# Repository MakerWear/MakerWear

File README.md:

# MakerWear
MakerWear is a tangible and modular, wearable construction kit for young children that contains two parts: (1) a set of single-function, plug-and-play modules that could be combined to create complex interactive behaviors; (2) magnetic socket meshes that are pre-sewn into clothing that provides an easy method to attach and detach modules to clothes.

This repository contains all of the source files that are required to build or modify MakerWear modules in addition to the socket mesh.

# Repository Organization
For example, take the MultiColor Light as an example. Similar to almost all other modules, the MultiColor Light is a 1x3 module which means that it has one input and three outputs and requires two PCBs to build. The bottom PCB is found here: https://github.com/MakerWear/MakerWear/tree/master/Common/BasePCBs/1x3/Bottom and the Top PCB (along with the rest of the source files that are specifically designed for this module) is found here: https://github.com/MakerWear/MakerWear/tree/master/Modules/Action/MultiColorLight

The ComponentList.xlsx contains all of the components and links to the vendors from which you can buy them. the .brd file (board layout) should always be next the the .sch file (board schematics).

Each module has a microcontroller which could be programmed using an Arduino. the arduino source file is inside the https://github.com/MakerWear/MakerWear/tree/master/Modules/Action/MultiColorLight/ArduinoCodes folder. and finally, there is an illustrator file which is used to cut/etch a piece of colored cardboard (e.g. white, red, black, blue for action, power, sensor and modifier) using a laser cutter.

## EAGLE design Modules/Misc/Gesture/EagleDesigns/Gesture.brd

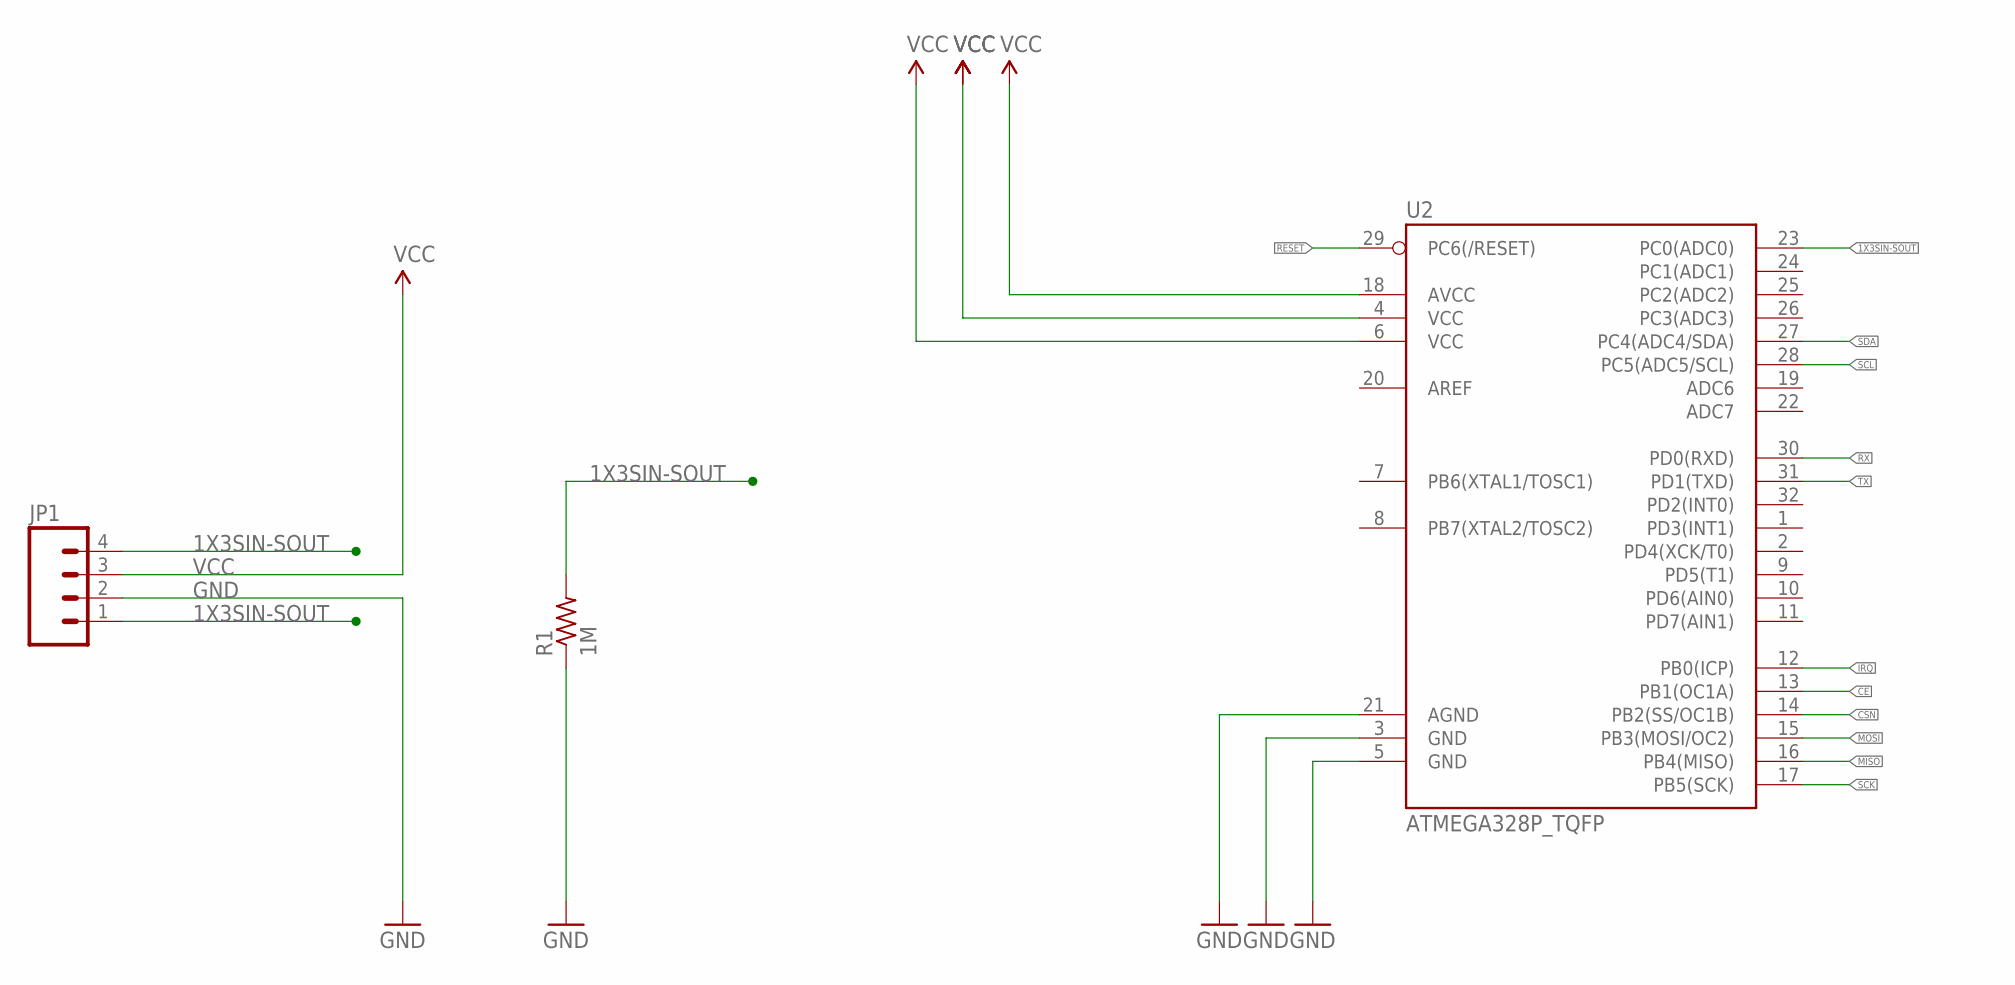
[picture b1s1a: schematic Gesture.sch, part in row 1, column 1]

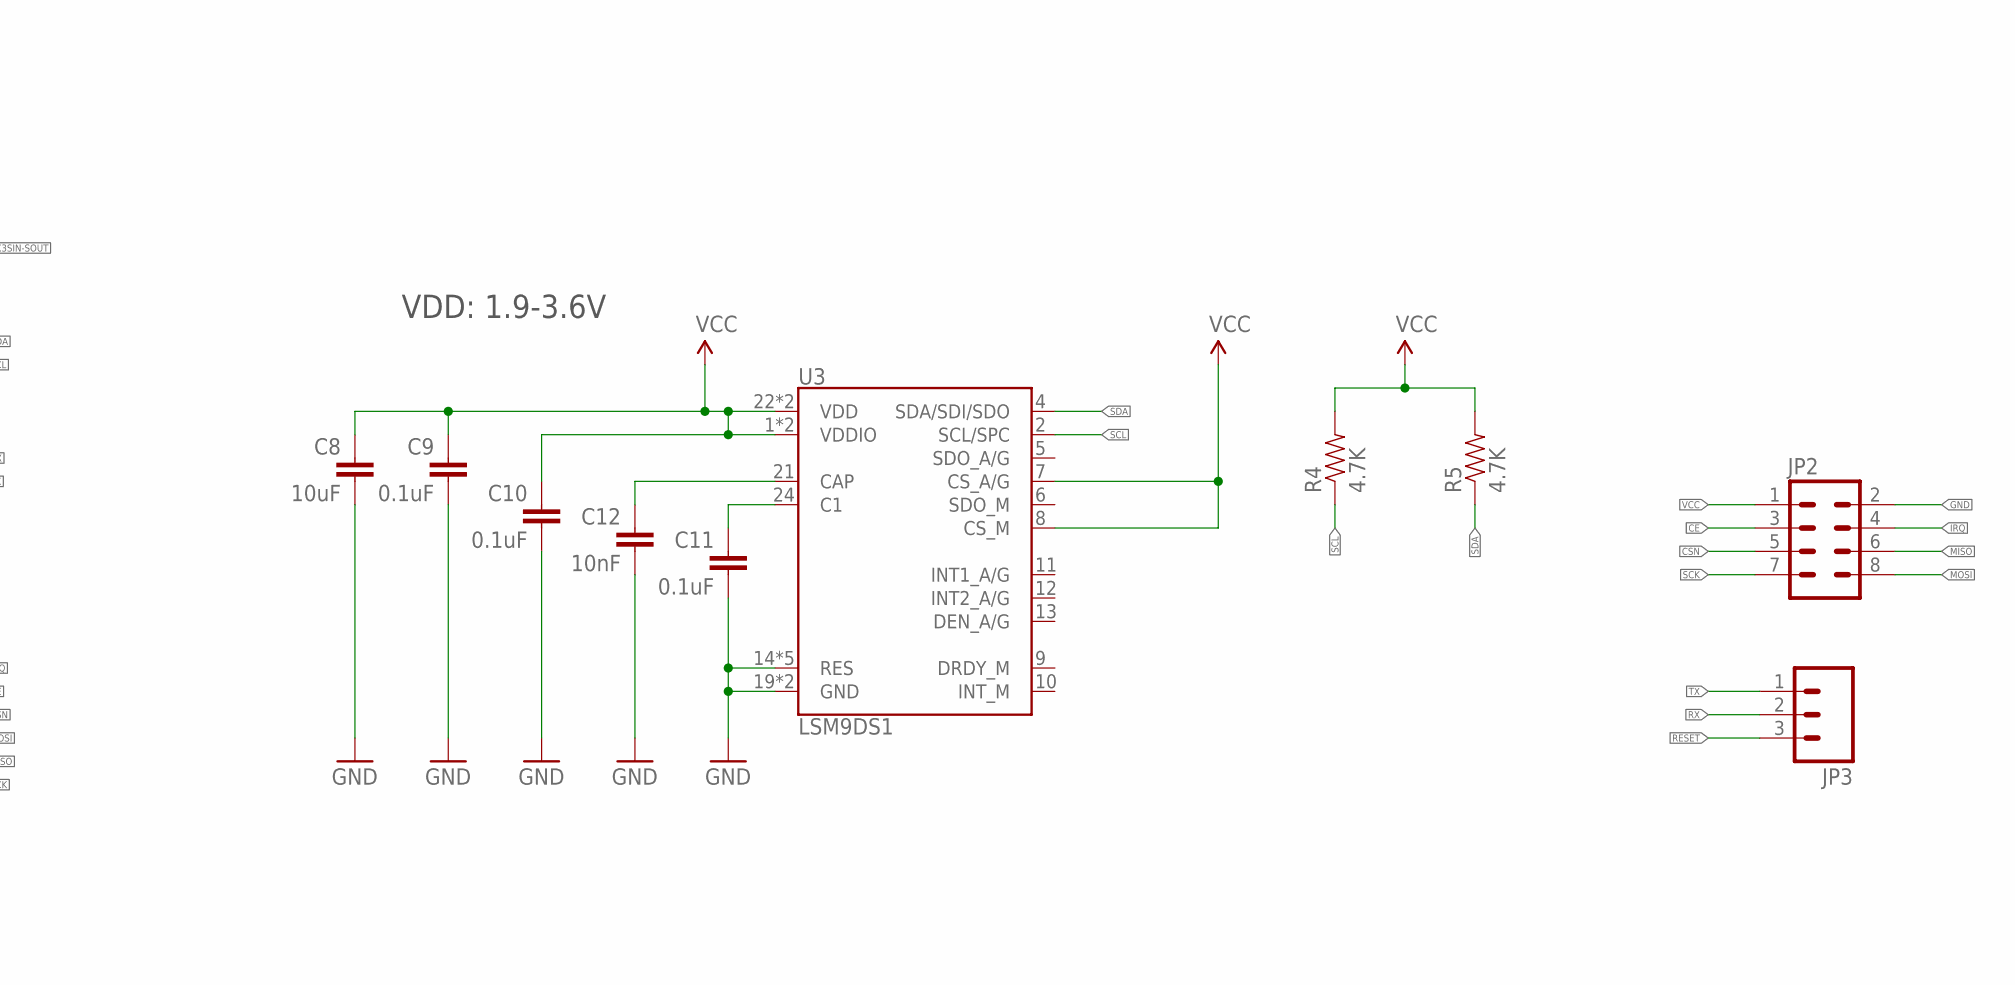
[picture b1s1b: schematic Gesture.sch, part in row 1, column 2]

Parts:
C8: 10uF; 0603-CAP
C9, C10, C11: 0.1uF; 0603-CAP
C12: 10nF; 0603-CAP
JP1: M04PTH; 1X04
JP2: M04X2_0.05"
JP3: M03PTH; 1X03
R1: 1M; R0603
R4, R5: 4.7K; 0603-RES
U2: ATMEGA328P_TQFP; TQFP32-08
U3: LSM9DS1; LGA24-8X4

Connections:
1X3SIN-SOUT: JP1.1, JP1.4, R1.2, U2.23 (PC0(ADC0))
CE: JP2.3, U2.13 (PB1(OC1A))
CSN: JP2.5, U2.14 (PB2(SS/OC1B))
GND: C8.2, C9.2, C10.2, C11.2, C12.2, JP1.2, JP2.2, R1.1, U2.3 (GND), U2.5 (GND), U2.21 (AGND), U3.14 (RES), U3.15 (RES), U3.16 (RES), U3.17 (RES), U3.18 (RES), U3.19 (GND), U3.20 (GND)
IRQ: JP2.4, U2.12 (PB0(ICP))
MISO: JP2.6, U2.16 (PB4(MISO))
MOSI: JP2.8, U2.15 (PB3(MOSI/OC2))
unnamed: C12.1, U3.21 (CAP)
unnamed: C11.1, U3.24 (C1)
RESET: JP3.3, U2.29 (PC6(/RESET))
RX: JP3.2, U2.30 (PD0(RXD))
SCK: JP2.7, U2.17 (PB5(SCK))
SCL: R4.1, U2.28 (PC5(ADC5/SCL)), U3.2 (SCL/SPC)
SDA: R5.1, U2.27 (PC4(ADC4/SDA)), U3.4 (SDA/SDI/SDO)
TX: JP3.1, U2.31 (PD1(TXD))
VCC: C8.1, C9.1, C10.1, JP1.3, JP2.1, R4.2, R5.2, U2.4 (VCC), U2.6 (VCC), U2.18 (AVCC), U3.1 (VDDIO), U3.3 (VDDIO), U3.7 (CS_A/G), U3.8 (CS_M), U3.22 (VDD), U3.23 (VDD)

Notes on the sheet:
VDD: 1.9-3.6V

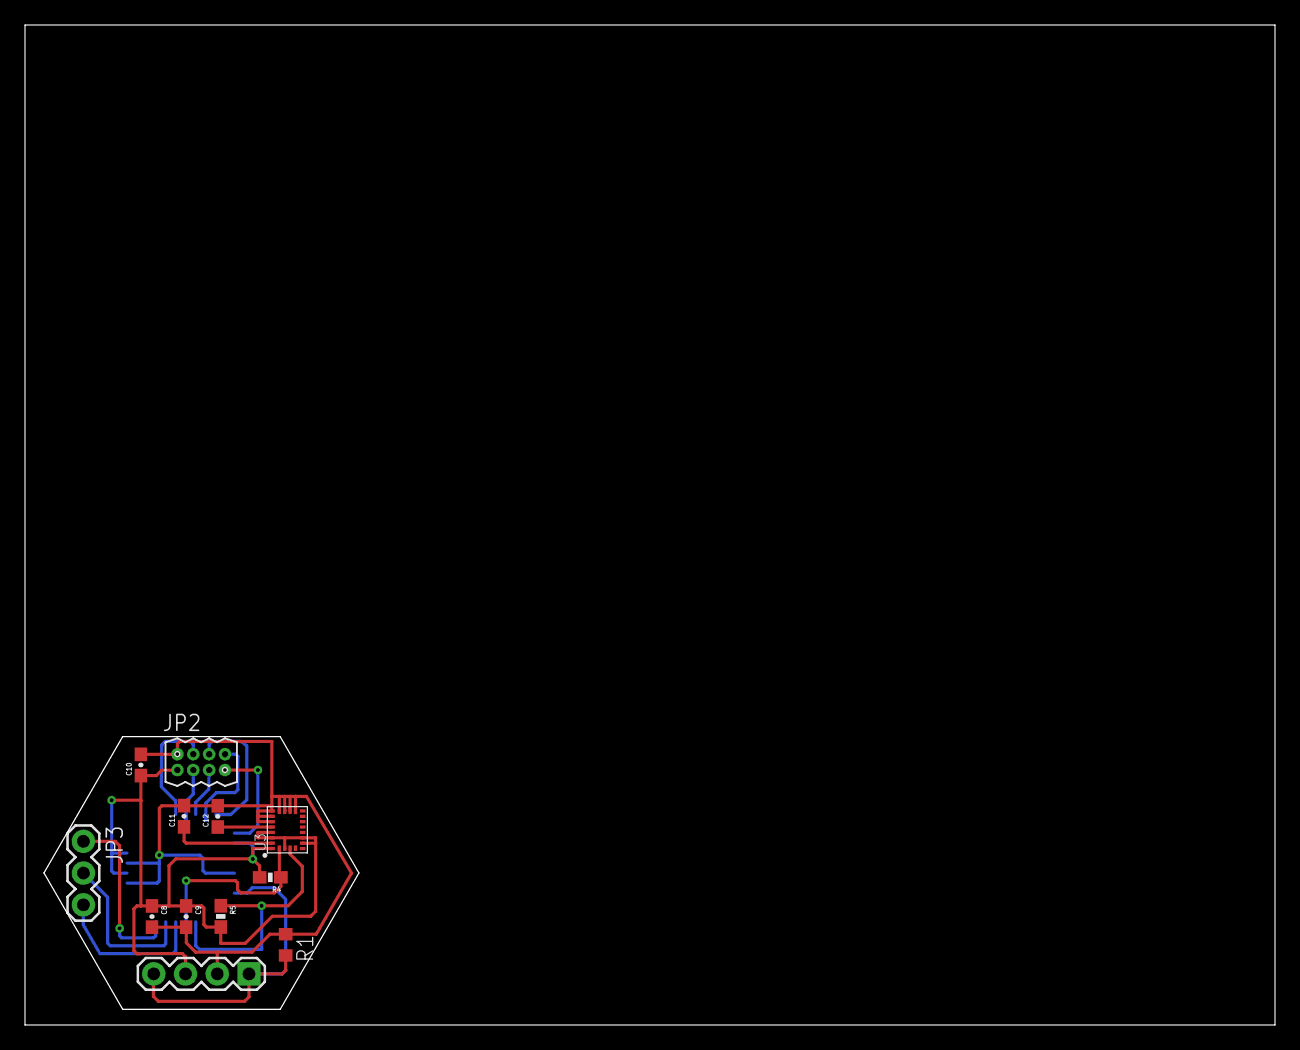
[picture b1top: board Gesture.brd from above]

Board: 2 copper layers, 100.0 x 80.0 mm, 13 parts (1 on the bottom side), 16 nets.

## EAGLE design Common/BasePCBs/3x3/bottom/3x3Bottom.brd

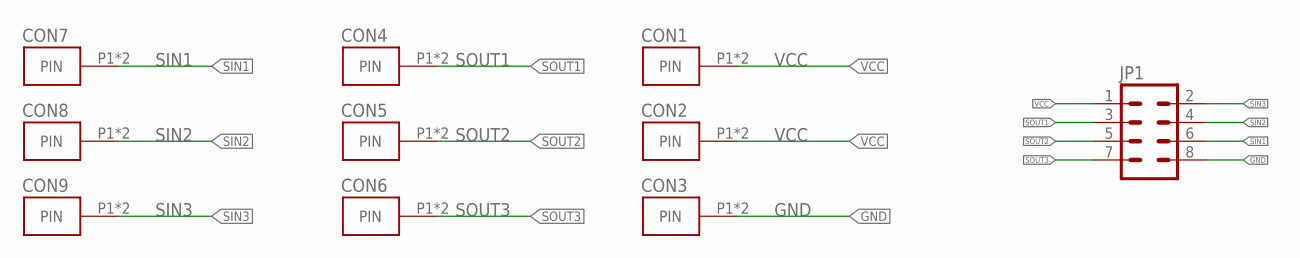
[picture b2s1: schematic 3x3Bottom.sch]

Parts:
CON1, CON2, CON3, CON4, CON5, CON6, CON7, CON8, CON9: SHIELD_FINGER0820; SHIELD_FINGER_PKG
JP1: M04X2_0.1"; M04X2_0.1"_PADS

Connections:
GND: CON3.P1, CON3.P2, JP1.8
SIN1: CON7.P1, CON7.P2, JP1.6
SIN2: CON8.P1, CON8.P2, JP1.4
SIN3: CON9.P1, CON9.P2, JP1.2
SOUT1: CON4.P1, CON4.P2, JP1.3
SOUT2: CON5.P1, CON5.P2, JP1.5
SOUT3: CON6.P1, CON6.P2, JP1.7
VCC: CON1.P1, CON1.P2, CON2.P1, CON2.P2, JP1.1

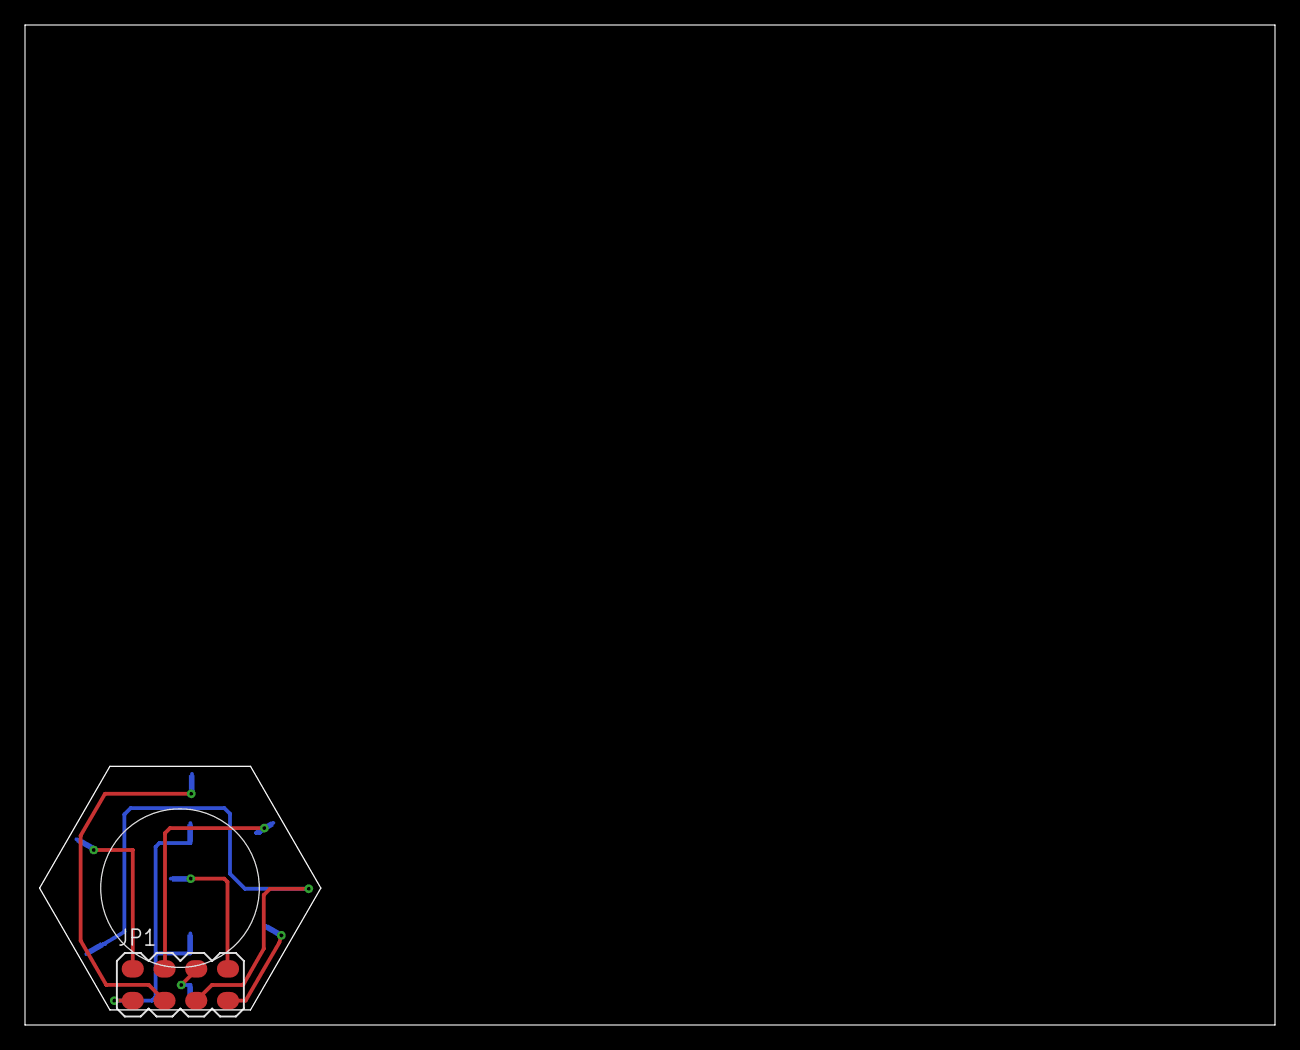
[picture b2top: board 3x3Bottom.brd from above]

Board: 2 copper layers, 100.0 x 80.0 mm, 10 parts (0 on the bottom side), 8 nets.

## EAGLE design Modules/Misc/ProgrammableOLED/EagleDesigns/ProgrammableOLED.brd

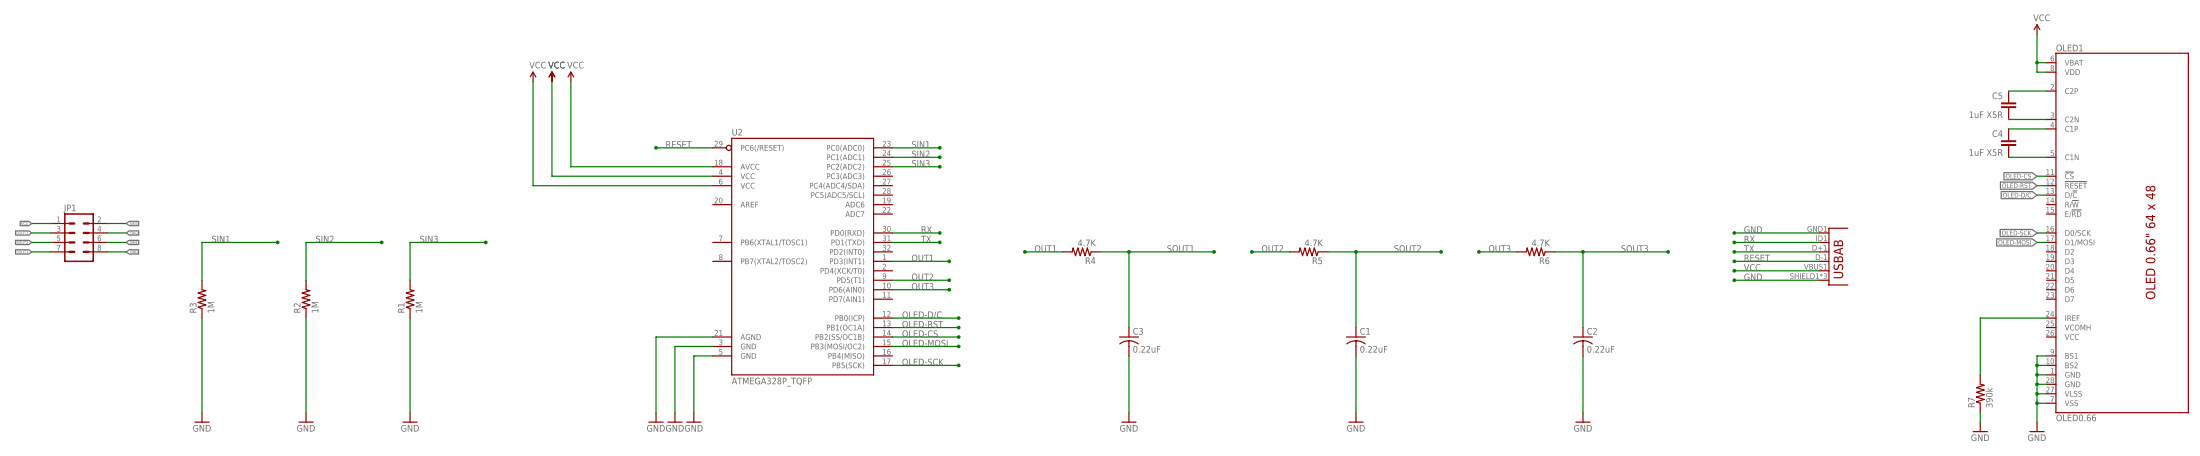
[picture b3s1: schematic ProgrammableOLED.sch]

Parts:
C1, C2, C3: 0.22uF; C0603
C4, C5: 1uF X5R; 0805
JP1: M04X2; 2X4
JP5: USB-ABCONN-11794; USB-AB-MICRO-SMD_V03
OLED1: OLED0.66; OLED-0.66-64X48
R1, R2, R3: 1M; R0603
R4, R5, R6: 4.7K; R0603
R7: 390k; 0603-RES
U2: ATMEGA328P_TQFP; TQFP32-08

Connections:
C1N: C4.2, OLED1.5 (C1N)
C1P: C4.1, OLED1.4 (C1P)
C2N: C5.2, OLED1.3 (C2N)
C2P: C5.1, OLED1.2 (C2P)
GND: C1.2, C2.2, C3.2, JP1.8, JP5.GND1 (GND), JP5.SHIELD1 (SHIELD), JP5.SHIELD2 (SHIELD), JP5.SHIELD3 (SHIELD), OLED1.1 (GND), OLED1.7 (VSS), OLED1.9 (BS1), OLED1.10 (BS2), OLED1.27 (VLSS), OLED1.28 (GND), R1.1, R2.1, R3.1, R7.1, U2.3 (GND), U2.5 (GND), U2.21 (AGND)
IREF: OLED1.24 (IREF), R7.2
OLED-CS: OLED1.11 (!CS!), U2.14 (PB2(SS/OC1B))
OLED-D/C: OLED1.13 (D/!C!), U2.12 (PB0(ICP))
OLED-MOSI: OLED1.17 (D1/MOSI), U2.15 (PB3(MOSI/OC2))
OLED-RST: OLED1.12 (!RESET!), U2.13 (PB1(OC1A))
OLED-SCK: OLED1.16 (D0/SCK), U2.17 (PB5(SCK))
OUT1: R4.2, U2.1 (PD3(INT1))
OUT2: R5.2, U2.9 (PD5(T1))
OUT3: R6.2, U2.10 (PD6(AIN0))
RESET: JP5.D-1 (D-), U2.29 (PC6(/RESET))
RX: JP5.ID1 (USBID), U2.30 (PD0(RXD))
SIN1: JP1.6, R3.2, U2.23 (PC0(ADC0))
SIN2: JP1.4, R2.2, U2.24 (PC1(ADC1))
SIN3: JP1.2, R1.2, U2.25 (PC2(ADC2))
SOUT1: C3.1, JP1.3, R4.1
SOUT2: C1.1, JP1.5, R5.1
SOUT3: C2.1, JP1.7, R6.1
TX: JP5.D+1 (D+), U2.31 (PD1(TXD))
VCC: JP1.1, JP5.VBUS1 (VBUS), OLED1.6 (VBAT), OLED1.8 (VDD), U2.4 (VCC), U2.6 (VCC), U2.18 (AVCC)

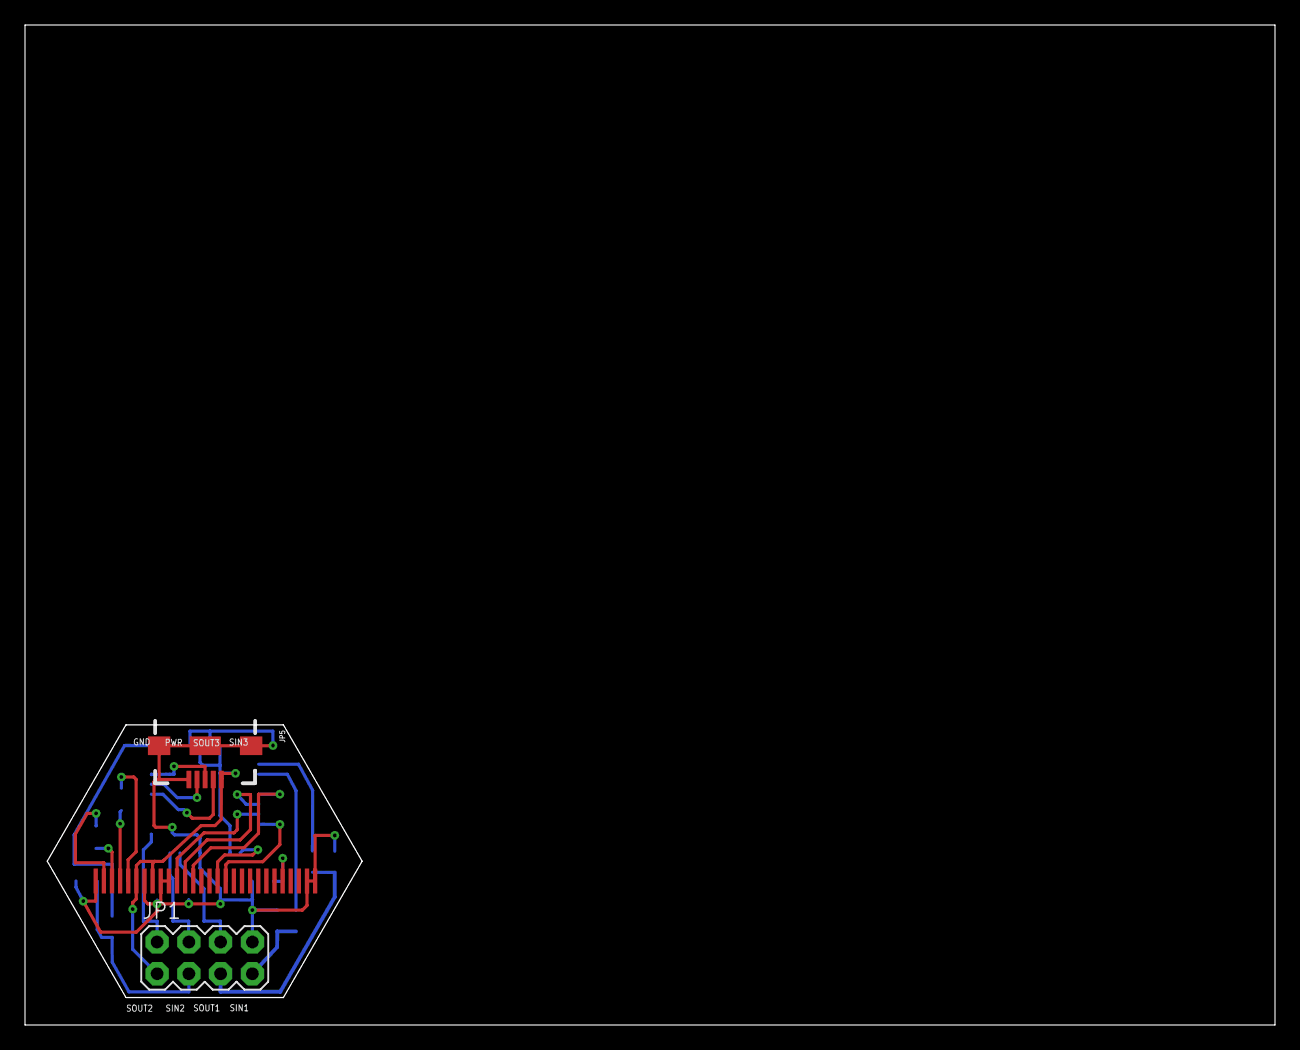
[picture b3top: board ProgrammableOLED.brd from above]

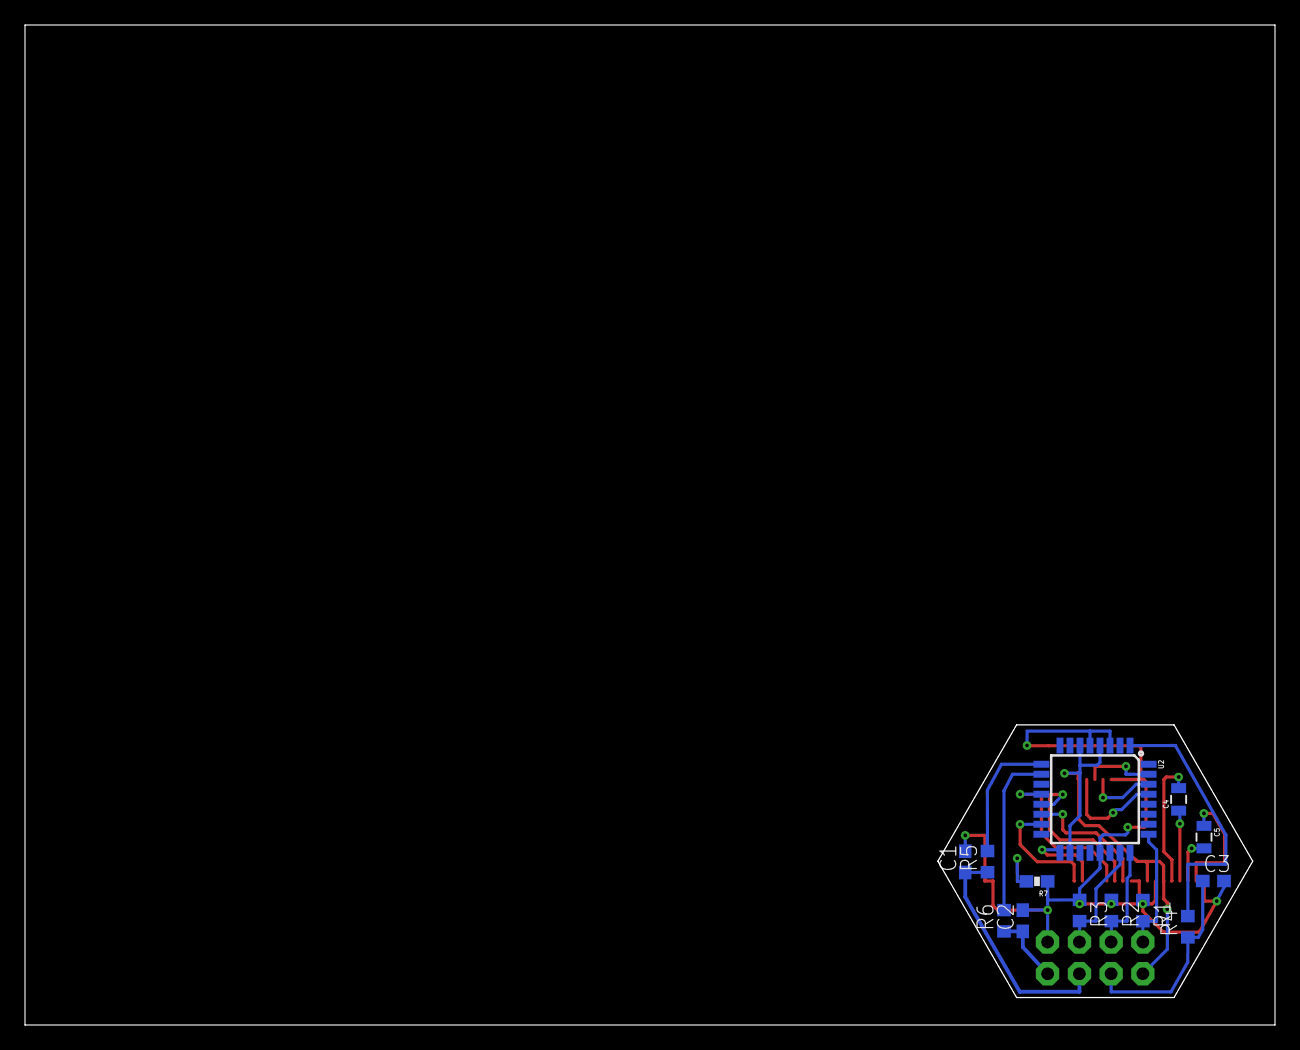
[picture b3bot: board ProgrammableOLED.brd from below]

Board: 2 copper layers, 100.0 x 80.0 mm, 16 parts (13 on the bottom side), 24 nets.

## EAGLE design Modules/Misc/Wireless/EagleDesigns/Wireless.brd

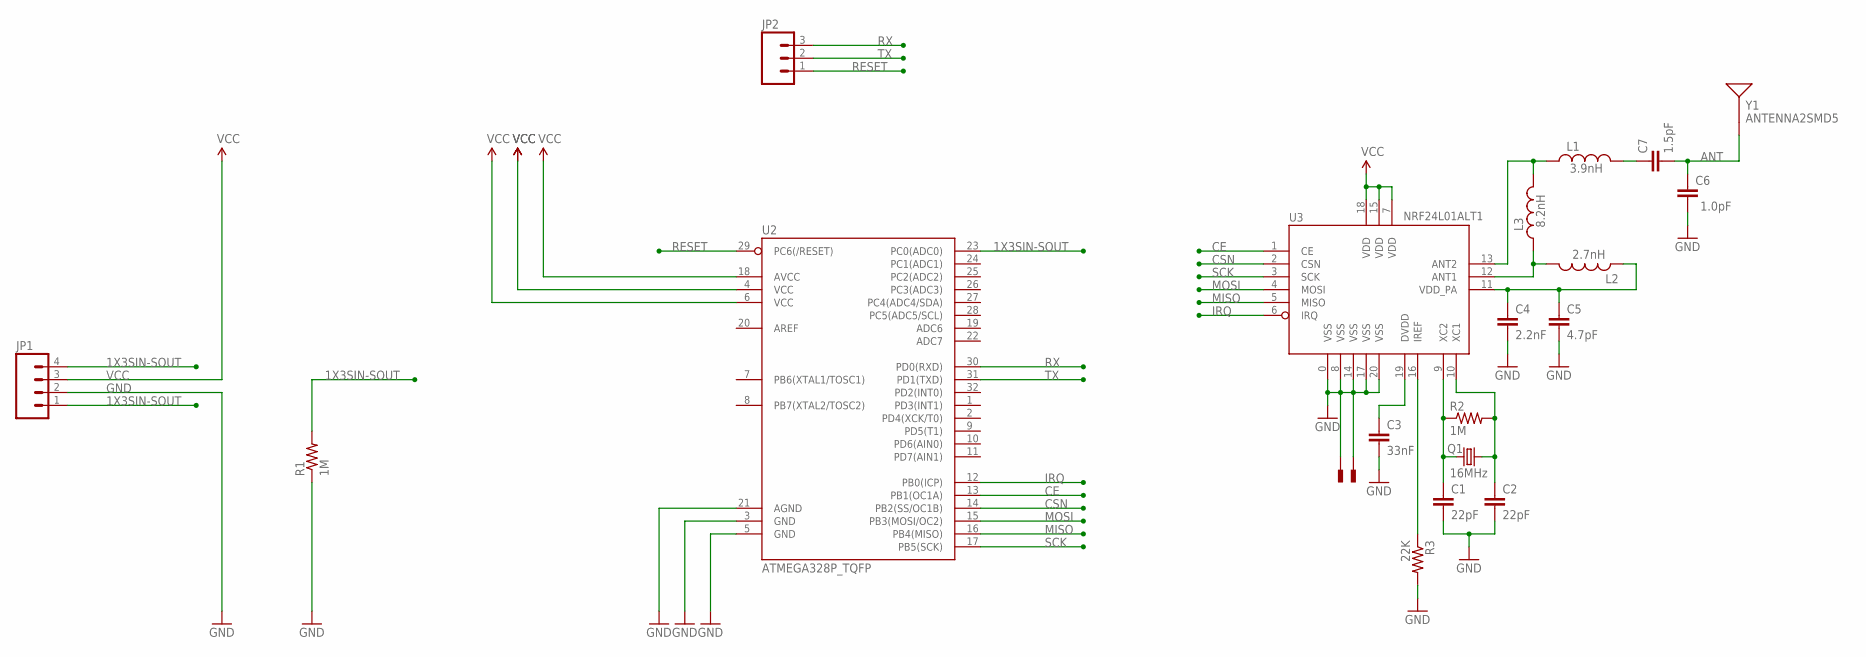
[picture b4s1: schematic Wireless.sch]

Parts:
C1, C2: 22pF; 0402-CAP
C3: 33nF; 0402-CAP
C4: 2.2nF; 0402-CAP
C5: 4.7pF; 0402-CAP
C6: 1.0pF; 0402-CAP
C7: 1.5pF; 0402-CAP
JP1: M04PTH; 1X04
JP2: M03PTH; 1X03
L1: 3.9nH; C0402
L2: 2.7nH; C0402
L3: 8.2nH; C0402
Q1: 16MHz; CRYSTAL-SMD-5X3
R1: 1M; R0603
R2: 1M; 0402-RES
R3: 22K; 0402-RES
U2: ATMEGA328P_TQFP; TQFP32-08
U3: NRF24L01ALT1; QFN20_ALT1
U$1, U$4: PAD; PAD-0.008
Y1: ANTENNA2SMD5; ANTENNA-CHIP5

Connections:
1X3SIN-SOUT: JP1.1, JP1.4, R1.2, U2.23 (PC0(ADC0))
ANT: C6.2, C7.2, Y1.FEED
CE: U2.13 (PB1(OC1A)), U3.1 (CE)
CSN: U2.14 (PB2(SS/OC1B)), U3.2 (CSN)
GND: C1.2, C2.2, C3.2, C4.2, C5.2, C6.1, JP1.2, R1.1, R3.2, U2.3 (GND), U2.5 (GND), U2.21 (AGND), U3.0 (VSS), U3.8 (VSS), U3.14 (VSS), U3.17 (VSS), U3.20 (VSS), U$1.P$1, U$4.P$1
IRQ: U2.12 (PB0(ICP)), U3.6 (IRQ)
MISO: U2.16 (PB4(MISO)), U3.5 (MISO)
MOSI: U2.15 (PB3(MOSI/OC2)), U3.4 (MOSI)
unnamed: C1.1, Q1.1, R2.1, U3.9 (XC2)
unnamed: C2.1, Q1.3 (2), R2.2, U3.10 (XC1)
unnamed: L2.2, L3.1, U3.12 (ANT1)
unnamed: R3.1, U3.16 (IREF)
unnamed: C3.1, U3.19 (DVDD)
unnamed: L1.1, L3.2, U3.13 (ANT2)
unnamed: C4.1, C5.1, L2.1, U3.11 (VDD_PA)
unnamed: C7.1, L1.2
RESET: JP2.1, U2.29 (PC6(/RESET))
RX: JP2.3, U2.30 (PD0(RXD))
SCK: U2.17 (PB5(SCK)), U3.3 (SCK)
TX: JP2.2, U2.31 (PD1(TXD))
VCC: JP1.3, U2.4 (VCC), U2.6 (VCC), U2.18 (AVCC), U3.7 (VDD), U3.15 (VDD), U3.18 (VDD)

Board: 2 copper layers, 21 parts (3 on the bottom side), 21 nets, no tracks yet.

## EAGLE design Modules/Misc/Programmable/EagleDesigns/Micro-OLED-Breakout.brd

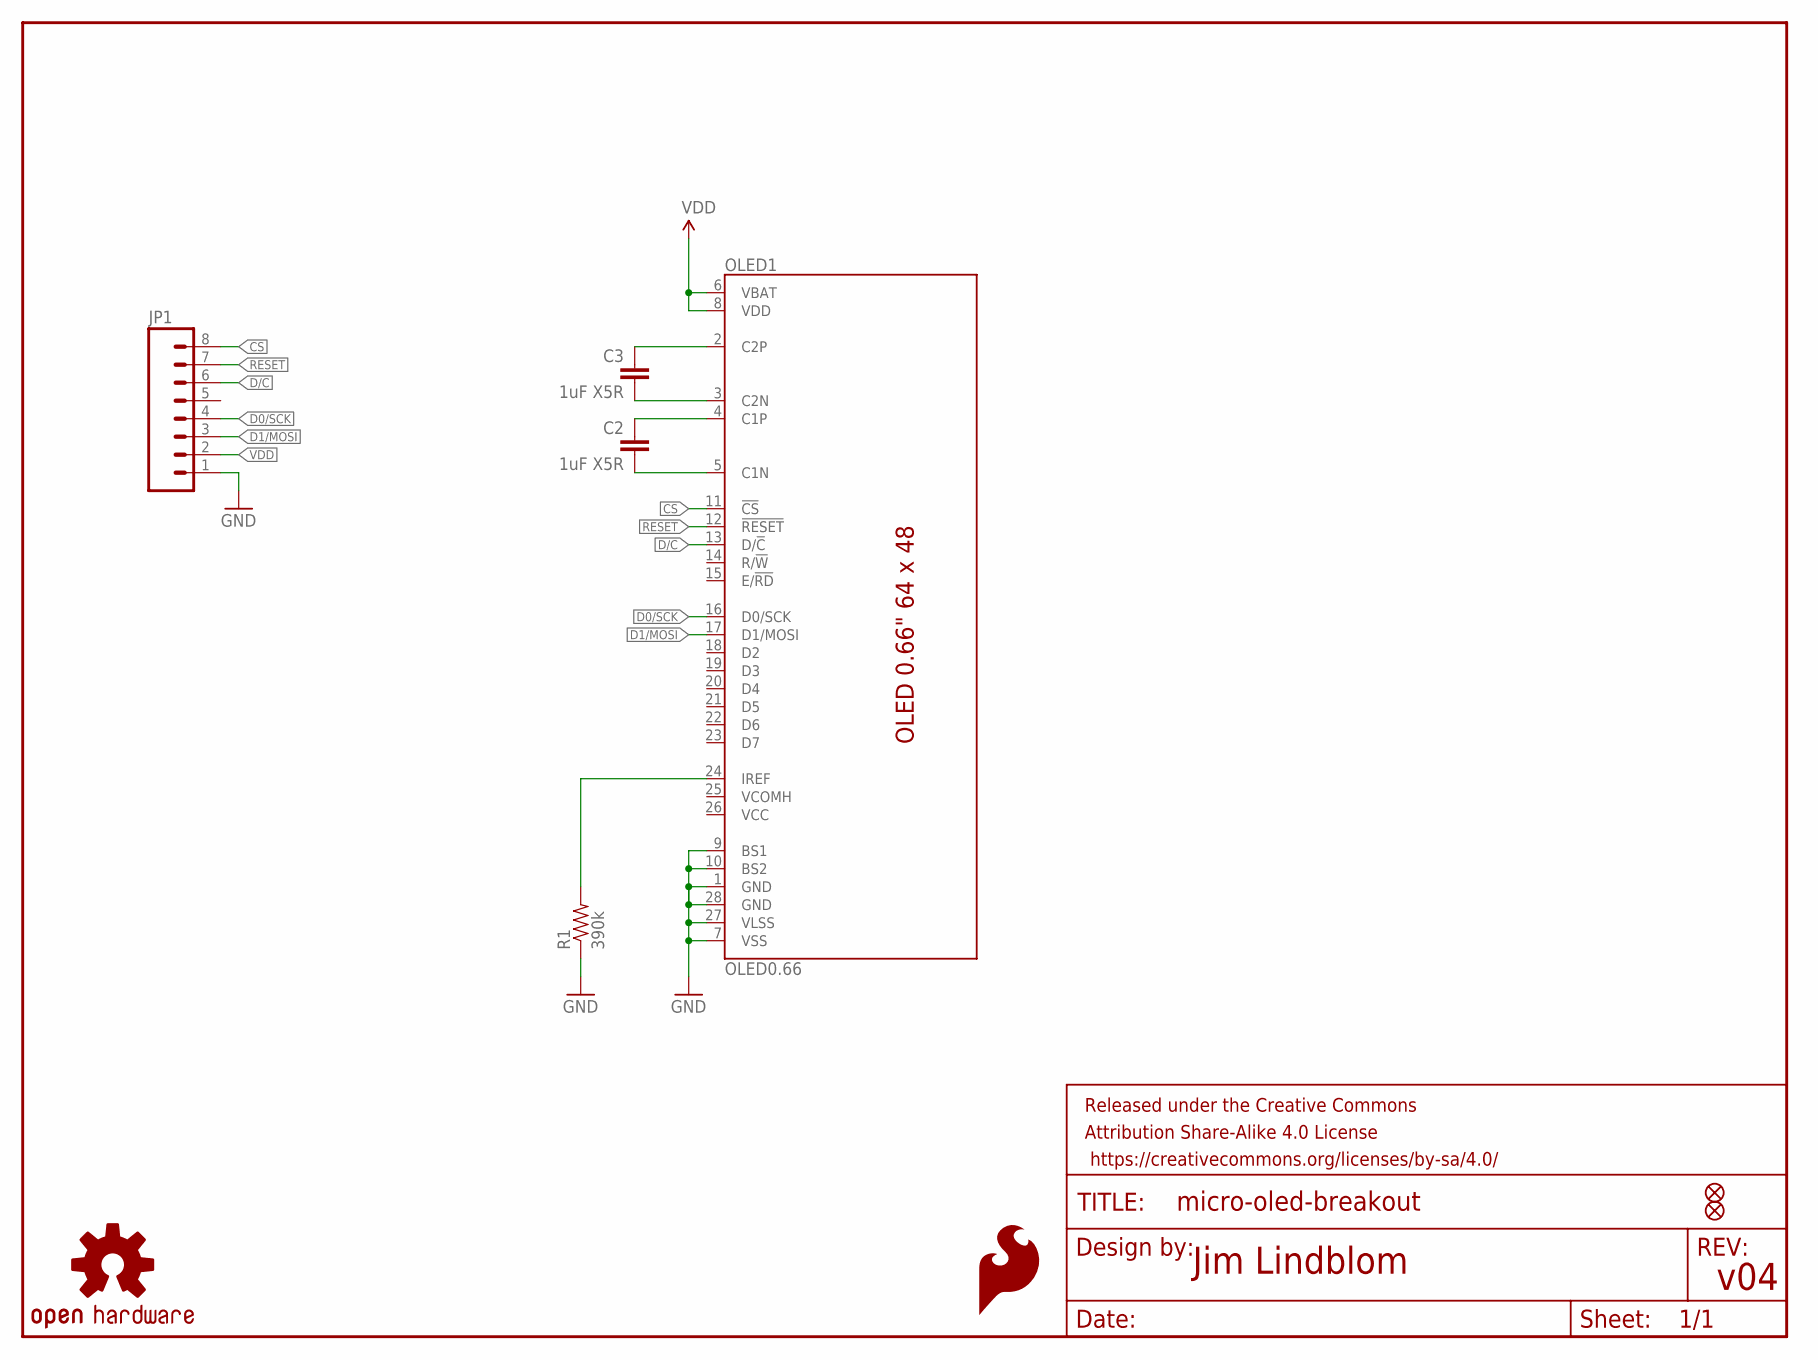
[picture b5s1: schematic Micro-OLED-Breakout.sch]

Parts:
C2, C3: 1uF X5R; 0805
FID1, FID2: FIDUCIAL1X2; FIDUCIAL-1X2
FRAME1: FRAME-LETTER; CREATIVE_COMMONS
JP1: M08; 1X08_PIN1_NO_SILK
LOGO3: OSHW-LOGOS; OSHW-LOGO-S
LOGO4: SFE_LOGO_FLAME.1_INCH; SFE_LOGO_FLAME_.1
OLED1: OLED0.66; OLED-0.66-64X48
R1: 390k; 0603-RES

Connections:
C1N: C2.2, OLED1.5 (C1N)
C1P: C2.1, OLED1.4 (C1P)
C2N: C3.2, OLED1.3 (C2N)
C2P: C3.1, OLED1.2 (C2P)
CS: JP1.8, OLED1.11 (!CS!)
D0/SCK: JP1.4, OLED1.16 (D0/SCK)
D1/MOSI: JP1.3, OLED1.17 (D1/MOSI)
D/C: JP1.6, OLED1.13 (D/!C!)
GND: JP1.1, OLED1.1 (GND), OLED1.7 (VSS), OLED1.9 (BS1), OLED1.10 (BS2), OLED1.27 (VLSS), OLED1.28 (GND), R1.1
IREF: OLED1.24 (IREF), R1.2
RESET: JP1.7, OLED1.12 (!RESET!)
VDD: JP1.2, OLED1.6 (VBAT), OLED1.8 (VDD)

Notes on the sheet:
v04
Jim Lindblom

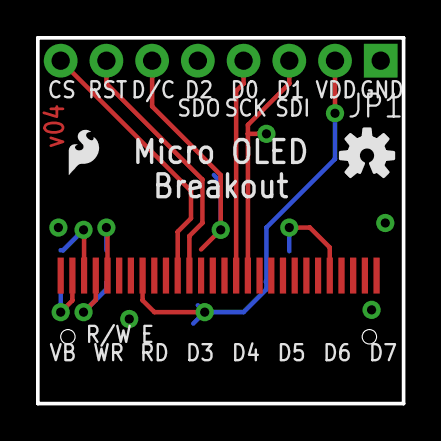
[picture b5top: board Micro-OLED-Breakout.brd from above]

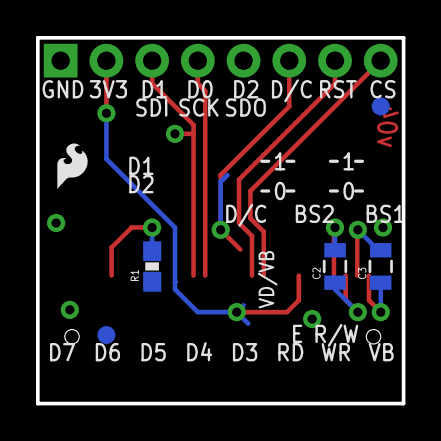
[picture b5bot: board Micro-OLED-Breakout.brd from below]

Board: 2 copper layers, 20.3 x 20.3 mm, 11 parts (6 on the bottom side), 12 nets.

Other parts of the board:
LOGO2: SFE_LOGO_FLAME.1_INCH; SFE_LOGO_FLAME_.1

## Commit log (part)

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2015-08-05 6 Modules added
    BarGraph, DistanceSensor, LightSensor, PianoSynthesizer, Pulse, RGB_LED
    The DistanceSensor is *NOT* updated with Tony’s latest version.
2015-08-10 Distance Sensor
    The output voltage is now affected by its input voltage.
2015-08-11 Added Impact Sensor (Smart)
2015-08-11 fixed sound sensor folder
2015-08-11 Revert "Added buggy Sound Sensor"
    This reverts commit 7c292b2102d95ad7382008a5954522c9bad4a963.
2015-08-11 Added Sound Sensor - ATtiny
2015-08-11 changes for new ir sender with potentiometer
2015-08-12 Added ATtiny TimeOut module
    And it worked :)
2015-08-15 distance sensor still not working perfectly :-(
2015-08-25 Fixed BarGraph Module
2015-08-25 minor changes to BarGraph Arduino
2015-08-25 minor commenting changes to RGB-LED
2015-08-25 Added Vibration Motor's code
2015-08-25 added pulse module
2015-08-25 Added Threshold
2015-08-25 Added Potentiometer Module
2015-08-25 changed minor comments
2015-08-26 Added Color Sensor
2015-08-27 minor commenting changes.
2015-10-21 fixed bar-graph mixed pins
    many problems in the PCB can be fixed with the code, like this one :)
2015-10-21 minor style modifications
2015-10-21 added UV light sensor libraries and module
2015-10-21 added timeout
2015-10-21 removed timeout, renamed it to fade
2015-10-22 UV Light Sensor, fixed and tested on ATtiny
2015-10-23 added base line code for TiltSensor
    TODO: need to update, test on Arduino and ATtiny85
2015-12-22 Added Sound Sensor
    It works perfectly on both Arduino and ATtiny85. TODO: test on PCB
2015-12-22 Minor Changes
2016-01-23 Added Impact Sensor
2016-01-25 TiltSensor
    Added debouncing code
2016-03-22 Sound Buzzer Update
2016-03-23 SoundBuzzer
    updated the last note!
2016-03-23 Light
    It now has an exponential light change in accordance to its input pin.
2016-06-02 added baseline code for the servo motor module
    it works on Arduino, but not on the ATtiny as the ATtiny does not have
    a 16bit timer
2016-06-02 added a working version of the Fade module
    it needs to update its output value upon receiving a new input pulse.
2016-06-02 changed the potentiometer to match its top cover
    changed it from 1023 -> 0 to 0 -> 1023.
2016-06-02 fixed to match the top cover
    again, instead of 1023 -> 0, it changes the threshold value from 0 ->
    1023 so that it would match the top cover that we designed.
2016-06-02 Light sensor is responsive to the module's input
    (e.g. when nothing is connected to it such as a power source, it should
    not work. Or a potentiometer before it should set the highest output
    voltage of the Light sensor’s output as well).
2016-06-02 still not working on ATtiny
2016-06-02 added temperature sensor
    which has a very low response rate (to changes in temperature) and thus
    will not be used.
2016-06-02 polished the UV Light Sensor's code
    removed that testing blink inside the setup, that would trigger
    whenever the module is inserted inside a socket.
2016-06-02 Revert "added ATtiny & ATmega base codes"
    This reverts commit 449d7c33cb42b075b19831fc93cc41e8839f986d.
2016-06-02 added ATmega and ATtiny base codes
2016-06-02 organized ActionModules
2016-06-02 organized Sensor modules
2016-06-02 added eagle files
2016-06-02 renamed OneInputThreeOutputConnection to 1x3Connection
2016-06-03 test
2016-06-03 testing
2016-06-03 Revert "test2"
    This reverts commit 2edd50fdcb88bedb9a702619717de426cbceaa0a.
2016-06-03 ImpactSensor: incorrect output value
2016-06-03 fixed #17
2016-06-03 fixed #16
2016-06-03 fixed #12
2016-06-03 fixed #14
2016-06-11 added Counter Module
    added the base code for the new Counter Module. It is compatible with
    all action modules, especially Number and LightBar.
2016-06-11 fixed #27
    the white LED will only be switched ON when the module is receiving
    HIGH input voltage. This makes the module (and the white LED) to be
    controlled using a button that could come before the module.
2016-06-12 added dimensions
    the illustrator (.ai) files and their drawing (.dxf) exports that could
    be read by the ULF reader. Also added the ULF eagle library to import
    .dxf files into eagle.
2016-06-12 re-organized dimensions
2016-06-12 added sender eagle files for #29
2016-06-12 added eagle files for #31
2016-06-13 added code for Sender
    tested on Arduino as well as ATmega328p.
2016-06-13 fixed the Fade module
    wasn't fading properly!
2016-06-13 designed Receiver's schematics
2016-06-13 added function prototypes
2016-06-13 Changed signal processing library names
2016-06-13 Modified the codes
    went through all module codes and changed FilteredAnalogInput to
    SignalProcessing and changed map to cutAndMap.
2016-06-13 Revert "Merge branch 'version-1.2'"
    This reverts commit 982d9c85d5bd00c48b539e840003de48d3cf178d, reversing
    changes made to b3895ae538c161df72313035d3e956c7a5ec4dbc.
2016-06-13 Added Wire Module
    Added schematic and board files for both wire_send and wire_receive
    modules
2016-06-14 finalized TemperatureReader layout for #31
2016-06-14 fixed fade module
2016-06-14 Rotator: added final PCB #30
2016-06-14 Receiver: added final PCB #29
2016-06-14 PulseSensor: added final PCB #40
2016-06-15 Added ATmega code for Number Module
2016-06-15 Rotator Module: Changed Servo Pin Number in Arduino
    In the Eagle schematic, the Servo is connected to Pin 9, not Pin 10
2016-06-15 Rotator: Changed Servo Pin
    In the Eagle schematic, the servo is connected to pin 9, not 10
2016-06-16 Added frequency module
2016-06-16 added comments
2016-06-16 Added IRremote library
2016-06-17 minor organizations
2016-06-17 changed 0403 cap to 0603 SMD cap
    to solder without difficulty!
2016-06-17 DIY Module: added version number #33
    and name on top of the PCB for documentation.
2016-06-17 Tweaked modifiers
    Changed fade so it only does it on HIGH pulses that come after LOW
    pulses. Finalized PulseMeter and made an ATtiny version of code.
2016-06-20 Corrected the Fade Module
    Did not work with the button at first. Also was not correctly using the
    LOW threshold.
2016-06-20 Changed Schematic for ATmega programming shield
    Added switch so board can be used for programming the bootloader and
    normal programs
2016-06-21 changed filter size on single LED
2016-06-22 Changed map function for vibration module
    Change range of map for output value to avoid "dead spot" when output to
    motor is close to zero
2016-06-22 fixed #10
    - added gamma table to the first LED on the LightBar
    - added states/thresholds for switching between colors
    (MultiColorLight), steps (LightBar) and notes (SoundMaker)
    - changed input filter size to 25 on all of them (MultiColorLight was
    25 previously)
2016-06-22 Removed delay for tilt sensor
2016-06-24 Fixed pulse sensor
2016-06-27 Sender & Receiver updates
2016-06-27 TemperatureReader: added base code
2016-06-27 Sender: added MK and AJ versions of the Sender module #29
2016-06-27 sender update
2016-06-27 Updated Receiver code
    now it outputs 0 when input is 0.
2016-06-29 Divided rotator positions into 18 steps
2016-06-29 Receiver: turns off when not receiving input
2016-06-30 Number: removed crystal, modified for new bootloader #49
    also added resistor to make sure that we address #49
2016-06-30 Receiver: removed crystal, modified to work with new bootloader #29
2016-06-30 Sender: removed crystal, modified to work with new bootloader
2016-06-30 added sine and saw wave modules
    still need some fine tuning
2016-06-30 Changed sender and receiver to transmit analog values #29
    Rather than dividing the transmission into 8 possible values, the sender
    now sends an analog value between 0 and 1023. Delay has been improved as
    well
2016-07-01 DistanceSensor: added another IR-TX LED #9
    to increase the range of the module.
2016-07-02 Programmer Shield: BoardLayout and Schematics for new bootloader
2016-07-05 Distance sensor turns off if 0 input
2016-07-06 Deleted stuff and renamed other stuff
    Deleted hybrid and triangle wave generators. Renames pulseMaker and
    SineWave to SquareGenerator and SineGenerator
2016-07-06 added comments to Sine generator
2016-07-08 Receiver: Fixed Merge Conflict
2016-07-10 Wiki: added header image
2016-07-10 re-organized files after Merge
2016-07-10 added pull-down resistor for Impact Sensor
    though we’re currently using the Tilt Sensor’s PCB for our current
    design.
2016-07-11 Temperature Reader: Won't output when input is 0
2016-07-11 Rotator: added 3D print OpenSCAD design #30
2016-07-13 Number: added cover design
2016-07-13 Rotator: added LEGO shaft openscad file
2016-07-13 Number: updated cover design
2016-07-13 Rotator: added top cover design
2016-07-13 DIY: added cover design #33
2016-07-13 Counter: added top cover design
2016-07-13 Sine/Square: added top cover design - closing #54
2016-07-13 Sender/Receiver: finalized top cover design - closing #29
2016-07-13 DIY: updated cover design
2016-07-13 DistanceSensor: finalized top cover design for new v1.2b module
2016-07-13 TemperatureSensor: updated sensor for the mlx90614 sensor
2016-07-14 Spinner: increased motor radius for cover
2016-07-14 Fade: updated top cover design
    thicker lines
2016-07-14 DistanceSensor: fixed top cover's dimensions
    to work with 3 IR LEDs
2016-07-14 ColorDetector: fixed top cover
2016-07-14 DIY: updated top cover design
2016-07-22 Changed Fade
    potentiometer values were reversed
2016-08-09 tuning on sound sensor
2016-08-09 Changed SoundSensor codes
    we now use a different method of determining when there is only
    background noise.
2016-08-09 slight changes in the top cover
2016-08-09 edited sound sensor
2016-08-10 Changed Sound Sensor
    Now uses a piecewise-linear mapping.
2016-08-11 DummyModule: Added LEGO peg .stl file
2016-08-11 Dummy: added top cover illustrator file
2016-08-12 Finalized Sound Sensor Code
    Scales output based on input value. Piecewise-linear mapping.
2016-09-28 added print-friendly module figures
2016-09-28 added 3x3 bottom PCB + schematics
    for the programmable/visualizer module
2016-09-30 Added programmable module's top PCB
2016-10-01 Programmable module: saved top cover!
2016-11-02 Added minimal schedmatic for SparkFun OLED display
2016-11-07 added old programmable module
    this is based on the
    https://www.seeedstudio.com/0.5-Inch-OLED-display-Arduino-shield-p-2194.
    html OLED display.
    The new version that I’m currently working on is based on the sparkfun
    OLED.
2016-11-08 added Micro-OLED library
2016-11-08 trying to make the wireless sender module to communicate with a computer
    didn’t work :-/
2016-11-14 added prototype debugging tool python script
2016-11-15 updated the Programmable module with the new OLED display
2016-11-15 updated the top PCB of the programmable module with a bigger PCB
    TODO: iterate and refine the top PCB
2016-11-28 added the new 3x3 PCBs
2016-12-01 updated the PCB
2016-12-02 added a larger version of the 1x3Top PCB
2016-12-02 started designing a self-contained IMU + ATmega328p + NRF24 Wireless module
2016-12-02 added the wirelessNRF24 hexagon shield for MakerWear modules
2016-12-03 finished the Gesture module
2016-12-05 increased rectangular copper widths to make it easier to fix/desolder
2016-12-05 fixed incorrect connections for the 3x3Bottom PCB
2017-01-14 Updated License to GPLv3
2017-01-17 added icons for every modules
    to be used in the wiki
2017-02-15 Update ColorDetectorATtiny.ino
    commented about the K-NN (k=1) prediction algorithm used to recognize the output color.
2017-05-16 reorganized the gesture module

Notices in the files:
parts and their libraries:
SparkFun-Connectors: Licensing: Creative Commons ShareAlike 4.0 International - https://creativecommons.org/licenses/by-sa/4.0
SparkFun-Aesthetics: Released under the Creative Commons Attribution Share-Alike 4.0 License
SparkFun-Aesthetics: https://creativecommons.org/licenses/by-sa/4.0
